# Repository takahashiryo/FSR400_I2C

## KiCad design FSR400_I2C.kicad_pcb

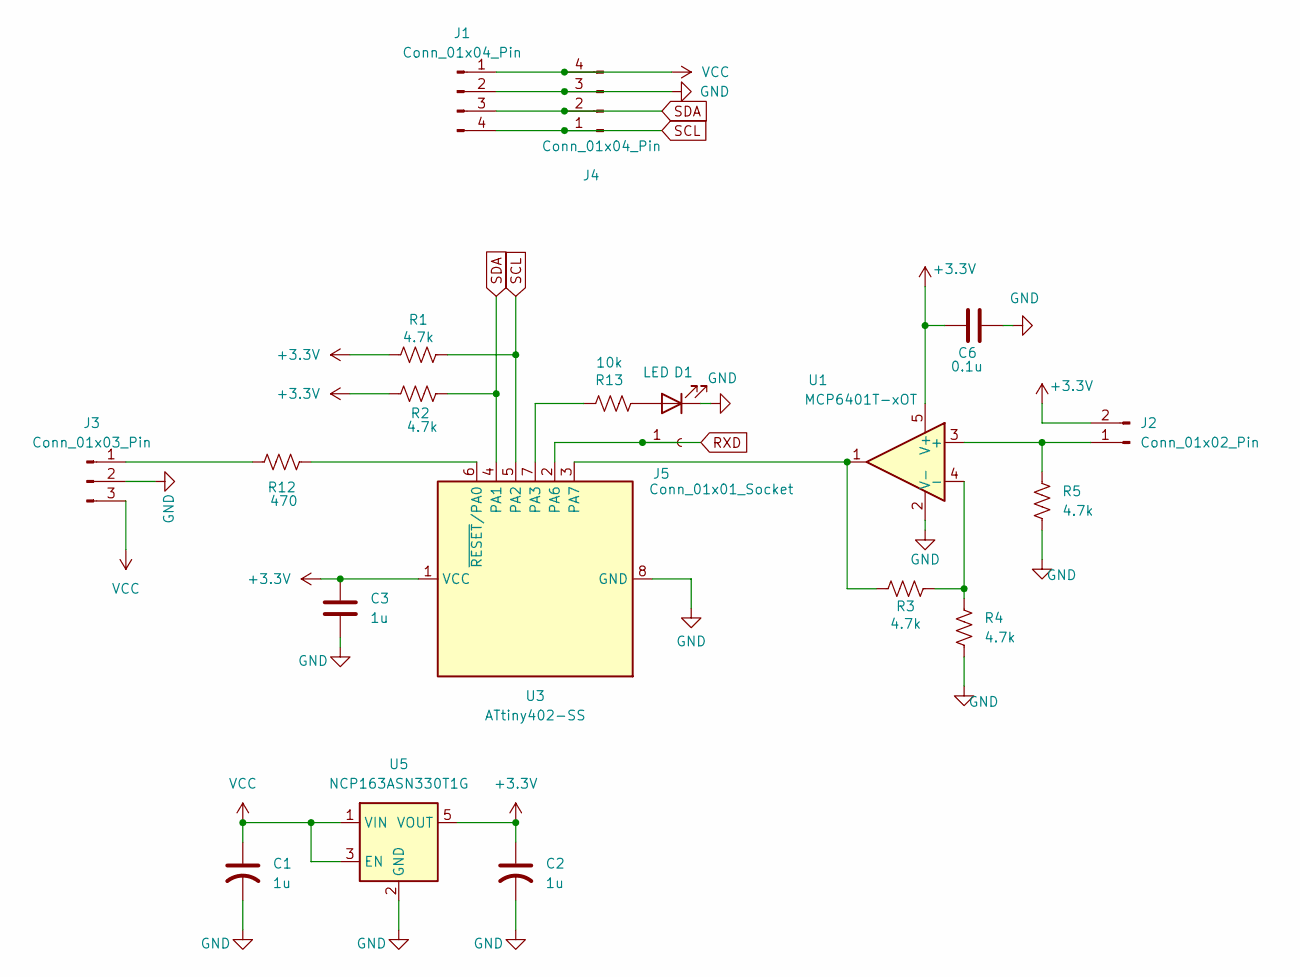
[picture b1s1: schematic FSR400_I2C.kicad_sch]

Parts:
C1, C2: 1u; C_0603_1608Metric_Pad1.08x0.95mm_HandSolder
C3: 1u; C_0402_1005Metric_Pad0.74x0.62mm_HandSolder
C6: 0.1u; C_0402_1005Metric_Pad0.74x0.62mm_HandSolder
D1: LED; LED_0402_1005Metric_Pad0.77x0.64mm_HandSolder
J1, J4: Conn_01x04_Pin; PinHeader_1x04_P2.54mm_Vertical
J2: Conn_01x02_Pin; PinHeader_1x02_P2.54mm_Vertical
J3: Conn_01x03_Pin; PinHeader_1x03_P2.54mm_Vertical
J5: Conn_01x01_Socket; PinHeader_1x01_P2.54mm_Vertical
R1, R2, R3, R4, R5: 4.7k; R_0402_1005Metric_Pad0.72x0.64mm_HandSolder
R12: 470; R_0402_1005Metric_Pad0.72x0.64mm_HandSolder
R13: 10k; R_0402_1005Metric_Pad0.72x0.64mm_HandSolder
U1: MCP6401T-xOT; SOT-23-5
U3: ATtiny402-SS; SOIC-8_3.9x4.9mm_P1.27mm
U5: NCP163ASN330T1G; SOT-23-5_HandSoldering

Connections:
+3.3V: C2.1, C3.1, C6.1, J2.2, R1.1, R2.1, U1.5 (V+), U3.1 (VCC), U5.5 (VOUT)
GND: C1.2, C2.2, C3.2, C6.2, D1.1 (K), J1.2, J3.2, J4.3, R4.1, R5.1, U1.2 (V-), U3.8 (GND), U5.2 (GND)
unnamed: D1.2 (A), R13.1
unnamed: J2.1, R5.2, U1.3 (+)
unnamed: J3.1, R12.2
unnamed: R3.2, R4.2, U1.4 (-)
unnamed: R13.2, U3.7 (PA3)
unnamed: R3.1, U1.1, U3.3 (PA7)
unnamed: R12.1, U3.6 (~RESET/PA0)
RXD: J5.1, U3.2 (PA6)
SCL: J1.4, J4.1, R1.2, U3.5 (PA2)
SDA: J1.3, J4.2, R2.2, U3.4 (PA1)
VCC: C1.1, J1.1, J3.3, J4.4, U5.1 (VIN), U5.3 (EN)

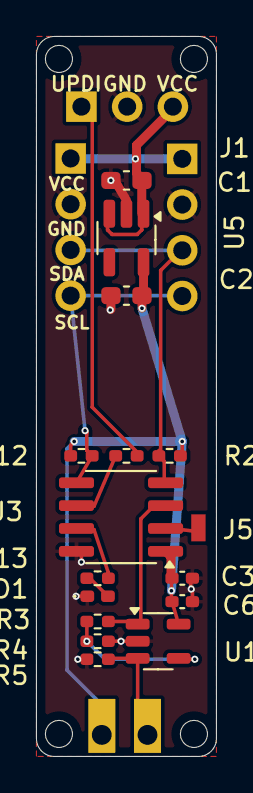
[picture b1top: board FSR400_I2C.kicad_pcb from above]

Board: 2 copper layers, 10.0 x 40.0 mm, 20 parts (1 on the bottom side), 13 nets.

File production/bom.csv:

Designator,Footprint,Quantity,Value,LCSC Part #
"C1, C2",0603,2,1u,
C3,0402,1,1u,
C6,0402,1,0.1u,
D1,0402,1,LED,
"J1, J4",PinHeader_1x04_P2.54mm_Vertical,2,Conn_01x04_Pin,
J2,PinHeader_1x02_P2.54mm_Vertical,1,Conn_01x02_Pin,
J3,PinHeader_1x03_P2.54mm_Vertical,1,Conn_01x03_Pin,
J5,PinHeader_1x01_P2.54mm_Vertical,1,Conn_01x01_Socket,
"R1, R2, R3, R4, R5",0402,5,4.7k,
R12,0402,1,470,
R13,0402,1,10k,
U1,SOT-23-5,1,MCP6401T-xOT,
U3,SOIC-8_3.9x4.9mm_P1.27mm,1,ATtiny402-SS,
U5,SOT-23-5_HandSoldering,1,NCP163ASN330T1G,

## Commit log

2025-06-24 Delete
